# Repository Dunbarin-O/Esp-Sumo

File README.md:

# Esp-Sumo
## Design Story

Building a custom mini-sumo robot sounded straightforward until i tried try wiring one together. Early in the process, I realized that relying on a disconnected stack of off-the-shelf motor drivers, sensor breakout boards, and external voltage regulators created a fragile spiderweb of jumper wires that easily disconnected during testing also pretty ugly, very ugly. To build something that stayed together, I decided to design a single, custom printed circuit board (PCB) to integrate every subsystem onto one reliable platform.

My first major challenge was in designing the power architecture. I initially planned to use two high-efficiency switching buck converters in series one to drop the 7.4V battery down to 5V, and a second to drop it further to 3.3V. While it looked ideal in block diagrams, routing the PCB layout showed that the second converter added significant cost, component count, and board space for a negligible boost in efficiency. I pivoted to a hybrid design: a single switching converter for high-draw 5V motor and servo demands, paired with a lightweight linear regulator for sensitive 3.3V logic. This trade-off taught me balancing performance, cost, and simplicity

Seeking external feedback proved equally transformative. After completing my first schematic draft, I had another hardware designer review my work. That peer review exposed critical real-world edge cases I had completely overlooked. To prevent catastrophic shorts during rapid battery swaps, I incorporated a low-resistance P-channel MOSFET switch for instant reverse-polarity protection. I also completely re-evaluated my motor drivers. My initial plan used tiny DRV8220 drivers to keep the board compact, but testing showed their high internal resistance caused severe overheating, and their strict overcurrent protection completely shut off power during motor stalls. I upgraded to dual DRV8870 drivers featuring active "current chopping." Instead of shutting down when pushing against an obstacle, the new drivers automatically throttle current to deliver maximum safe pushing force without crashing the battery rail.

When the fabricated boards arrived, the ESP32-S3 microcontroller powered on and flashed code over USB smoothly on the first try. However, physical hardware quickly revealed real-world oversights that software DRC checks could not predict. I had selected incorrect physical footprints for my pin headers in KiCad, meaning the OLED display could not plug directly into the board and required manual jumper wire reworks. Furthermore, placing every component on a single side made the overall PCB footprint far too large for a compact mini-sumo chassis.

This project proved that a circuit can look entirely correct in a schematic editor while real-world physics, ergonomics, and physical dimensions tell a different story. Version 1 was not perfect, but it served as a functional masterclass in circuit protection, component selection, and practical board layout. For Version 2, I am transitioning to a double-sided component layout to cut the board size in half while correcting all header footprints for a clean, plug-and-play assembly.
---

### Read Further

For detailed technical implementation, schematics, component calculations, PCB layout files, and manufacturing outputs, explore the rest of the repository which is still a wip :

* **`PCB/`** – Native KiCad design files:
  * `Mini_sumo.kicad_sch` – Schematic capture files.
  * `Mini_sumo.kicad_pcb` – PCB trace routing and board layout.
* **`Hardware/`** – Assembly and manufacturing outputs:
  * `Mini_sumo.zip` – Production Gerber & drill files for board fabrication.
  * `combined_bom.csv` – Bill of Materials listing all active and passive components.
  * `positions.csv` – Pick-and-Place (CPL / Centroid) file for automated SMT assembly.
Project is in
 its early stages 

A low-cost, open-source motion control board for ESP32-based robots.
High-performance motor boards are usually expensive or made for just one job. This project is a low-cost, all-in-one board that lets you build precise small robots without needing extra shields or breakout boards.

Applications:

Mini Sumo Robots: Integrated motor control and gyro feedback for rapid opponent tracking and high-torque maneuvers.

Inverted Pendulum / Self-Balancing: Direct IMU integration for low-latency loop control and pitch stabilization.

Heading-Corrected Rovers: Closed-loop yaw monitoring for straight-line differential driving and precise turn angles.

### V1 Key Features

* **Dual High-Current Motor Drivers:** Two TI DRV8870 ICs providing independent PWM speed and direction control, supporting up to 3.6 A peak output per channel.
* **Onboard Motion Sensing:** MPU-6050 6-axis gyroscope and accelerometer connected via I2C for pitch, roll, and yaw feedback.
* **Integrated Diagnostic Display Header:** Dedicated 4-pin I2C header positioned for direct SSD1306 OLED screens (128x64 or 128x32).
* **User Input Controls:** 3 onboard tactical pushbuttons mapped to ESP32 GPIOs for mode selection, calibration, and menu navigation.
* **Built-in Servo Mount & Header:** Dedicated 3-pin PWM servo header (VCC, GND, Signal) with mounting holes integrated directly into the PCB outline (ideal for mini sumo flippers or sensor sweepers).
* **Optimized Power Architecture:** Designed for 2S (7.4V) LiPo input with onboard voltage regulation to safely power the ESP32, OLED, and logic components.
* **Expansion I/O:** Exposed GPIO headers for IR edge sensors, line detectors, or custom sensors.
* **100% Open-Source Hardware:** Full KiCad project files, schematics, PCB layouts, BOM, and manufacturing outputs (Gerbers/CPL) included.

| ESP32-S3 GPIO | Schematic net | Actually connected to             |
| ------------: | ------------- | --------------------------------- |
|     **GPIO0** | I00           | Boot button **SW3** + 10k pull-up |
|     **GPIO1** | D1            | **Right IR sensor** J5            |
|     **GPIO2** | D2            | **Left IR sensor** J6             |
|     **GPIO3** | D3            | **SW4 button**                    |
|     **GPIO4** | D4            | **Left edge sensor** J8           |
|     **GPIO5** | D5            | **Right edge sensor** J10         |
|     **GPIO6** | D6            | **SW5 button**                    |
|     **GPIO7** | D7            | **SW6 button**                    |
|     **GPIO8** | D8            | **Left motor driver IN2**         |
|     **GPIO9** | D9            | **Left motor driver IN1**         |
|    **GPIO10** | D10           | **J17 breakout pin 1**            |
|    **GPIO11** | D11           | **Gyro SCL**                      |
|    **GPIO12** | D12           | **Gyro SDA**                      |
|    **GPIO13** | D14           | **Right motor driver IN2**        |
|    **GPIO14** | D13           | **Right motor driver IN1**        |
|    **GPIO15** | D15           | **J15 / right motor?**            |
|    **GPIO16** | D16           | **J11 servo?**                    |
|    **GPIO17** | D17           | **J17 software uvlo**             |
|    **GPIO18** | D18           | **Servo signal**                  |
|    **GPIO19** | USB_D−        | **USB D−**                        |
|    **GPIO20** | USB_D+        | **USB D+**                        |
|    **GPIO21** | —             | **Unused**                        |

 ## Engineering Design Process & Iterations
## Power Design Choice: Dual Buck Converters vs. Buck + LDO

### First Attempt: Two-Stage Buck Regulation
My initial plan was to use two buck converters in series to drop the 7.4V (2S LiPo) battery voltage down to 5V, and then down to 3.3V for the system ICs to maximize energy efficiency.

**The Problem:** Each buck converter requires its own dedicated supporting passives (inductors, filter capacitors, and feedback resistors). Running two switching stages took up too much PCB footprint, added significant routing complexity, and increased the overall Bill of Materials (BOM) cost.

---

### Final Solution: Single Buck + 3.3V LDO Regulator
I simplified the power tree by keeping a single buck converter for the 5V rail and replacing the second buck stage with a straightforward 3.3V Low-Dropout (LDO) linear regulator.

## Peer Design Review: Power & Protection Enhancements

Following the V1 layout release, a community hardware review identified several critical power delivery and protection improvements to increase reliability:

### 1. Battery Input & System Protection
* **Circuit Protection:** The design was solid, but it lacked input safety. Adding an in-line fuse and a reverse-polarity protection circuit (e.g., a P-channel MOSFET or ideal diode) on the 2S LiPo rail is essential to prevent permanent board failure from accidental battery misplugs during quick pit stops.
* **Input Bulk Decoupling:** The 10 µF input capacitor ($C_{\text{IN}1}$) on the buck regulator followed basic bench-supply reference designs. However, long battery wire harnesses introduce parasitic inductance. Upgrading $C_{\text{IN}1}$ to a **47 µF ceramic + 10 µF ceramic paired with a 100 µF electrolytic** lowers High-Frequency ESR and prevents sudden motor current draw from sagging the shared battery rail and browning out the ESP32.

### 2. Switching Regulator Duty Cycle & Stability
* At 7.4 V nominal input, the 5 V buck converter operates near a **0.67 duty cycle** (higher as the LiPo drains). Because the regulator uses peak current mode with fixed internal compensation, switch-node signal integrity must be verified under full load with an oscilloscope to ensure stable loop performance across the entire discharge curve.

### 3. ESD & Port Safety
* Added dedicated **ESD protection IC (USBLC6-2SC6)** on the USB-C $V_{\text{BUS}}$ and $D+/D-$ lines to guard the ESP32 against static discharge during  flashing
* 

### Power Isolation: OR-ing Diode Selection

To prevent backfeeding power between the USB-C 5V supply and the onboard 5V buck converter when both are plugged in simultaneously, I implemented a simple diode OR-ing power path
combining the 2 into 5V Safe and feeding it into ldo.

* **Why Schottky over Silicon Diodes:** Standard silicon rectifiers cause a ~0.7V drop, which would reduce the 5.0V USB rail down to 4.3V—dangerously close to the ESP32's minimum operating threshold and brownout limit.
* **Low Forward Voltage ($V_F$):** Using Schottky diodes keeps the voltage drop under ~0.3V, maintaining a stable supply rail (~4.7V+) for logic components and sensors while safely preventing reverse current flow into your computer's USB port or the buck regulator since a lipo battery is used trying to charge over usb withour any charging circuits could be dangerous.
  
### Front-End Power Protection Circuit

* **P-Channel Reverse Polarity Protection (AO3401A):** Uses a low-$R_{DS(on)}$ P-FET (Q1) to block reverse voltage if the battery is plugged in backward, with a 10V Zener diode (D1) protecting $V_{GS}$ against voltage transients.
* **Overcurrent Safety (F1):** In-line fuse provides hard fault protection against high-current shorts.
* **Active Under-Voltage Monitoring (TPS3702):** Samples battery rail via resistor divider (R21/R22) and outputs a low-battery alert signal (D17) to the ESP32 to prevent over-discharging 2S LiPo cells.
* 
## Picking a driver IC : DRV8220 vs. DRV8870

When designing the motor stage, I needed driver chips capable of handling high startup currents and heavy mechanical loads without overheating or shutting down mid-operation.

### First Attempt: Dual DRV8220 (Compact, but Limited)

My initial plan was to use two compact DRV8220 drivers in the DRL package, but bench analysis revealed major bottlenecks:
* **Thermal Overheating:** High internal resistance ($R_{DS(on)} \approx 1\,\Omega$) and the lack of a thermal pad ($152\,^{\circ}\text{C/W}$ thermal resistance) caused severe heat buildup, limiting continuous current to $< 0.9\text{A}$.
* **Hard Shutdowns:** The $1.76\text{A}$ overcurrent protection (OCP) cuts power entirely during high loads or stalls, stopping the robot mid-operation instead of sustaining torque.
* **Difficult Hand-Soldering:** The tiny leadless DRL package has contacts tucked under the chip, making it extremely difficult to solder, inspect, or rework with a standard soldering iron without bridging.
* **No Built-in Current Sensing:** Lacks a dedicated `ISEN` pin, preventing the use of external sense resistors to measure or actively control motor current.
* **Startup Voltage Glitches & Efficiency Loss:** Logic inputs easily float during microcontroller boot, causing motor twitches. High internal resistance also wastes battery voltage as heat before it reaches the motors.

---

### Final Solution: Dual DRV8870 (High Power & Current Chopping)

I upgraded to two DRV8870 drivers featuring an exposed PowerPAD package and external sense resistors:
* **Hand-Soldering Friendly:** The larger HSOP-8 package with exposed leads **very** important for reliable hand soldering(ended up having it assembled by jcl).
* **Superior Thermals:** Lower internal resistance ($450\,\text{m}\Omega$) paired with a copper thermal pad handles up to $3.6\text{A}$ peak current safely.
* 

* **Smart Current Chopping ($I_{\text{TRIP}}$):** Instead of shutting down completely during a stall, the driver uses parallel sense resistors ($R17 - R20$) totaling $0.2\,\Omega$ to limit current automatically:
  $$I_{\text{TRIP}} = \frac{V_{\text{REF}}}{10 \times R_{\text{ISEN}}} = \frac{3.3\text{V}}{10 \times 0.2\,\Omega} = 1.65\text{A}$$
  When pushing heavy loads, the chip acts like an automatic safety valve "chopping" current to maintain pushing force without tripping power failures or browning out the battery rail.
* **Brush Noise Suppression:** Added $0.1\,\mu\text{F}$ ceramic capacitors ($C2, C5$) directly across the motor terminals to absorb high-frequency electrical noise before it can interfere with the I2C gyroscope or IR floor sensors.

---
## ESP32-S3 Core
i chose the s3 because of its native usb to uart and it simplicity to set up and get working keeping parts cost low

This section covers the core ESP32-S3 microcontroller, its power filtering, boot/reset logic, user UI, and external expansion headers.

### Core Microcontroller (ESP32-S3-WROOM-1)
* **Brain of the Robot:** Handles sensor polling, motor control loops, and peripheral interfaces.
* **Power Decoupling ($C14, C15$):** Placed $0.1\,\mu\text{F}$ and $22\,\mu\text{F}$ capacitors close to the $+3.3\text{V}$ power pin (`Pin 2`) to filter out high-frequency noise and prevent voltage dips when the chip spikes in power draw during wireless tasks or bootup.

---

### Boot Logic & System Buttons
* **Reset Circuit (`SW2`, `EN`):** Pressing `SW2` pulls the `EN` pin to ground to manually restart the microcontroller. 
  * **Debouncing & RC Delay ($R9, C9, C13, R13$):** An RC circuit ($10\,\text{k}\Omega$ pull-up + $1\,\mu\text{F}$ cap) keeps `EN` stable at $+3.3\text{V}$ and prevents electrical noise from causing random micro-resets.
* **Boot Button (`SW3`, `IO0`):** Pressing `SW3` grounds `IO0` on startup to force the ESP32 into USB flashing/bootloader mode. A $10\,\text{k}\Omega$ pull-up resistor ($R14$) ensures `IO0` stays pulled HIGH during normal operation so the chip boots standard code.

---

### User UI & Peripherals
* **User Pushbuttons (`SW4`, `SW5`, `SW6`):** Standard tactile buttons tied to `D3`, `D6`, and `D7`. When pressed, they ground the input line, giving the user programmable controls (e.g., selecting robot fight modes or starting a match).
* **Status LED (`D6`, $R15$):** A debug LED connected to $+3.3\text{V}$ via a $1\,\text{k}\Omega$ current-limiting resistor ($R15$) for visual feedback.

---

### Breakout & Expansion Headers
* **Power Breakouts (`J7`, `J9`):** 4-pin headers giving easy access to GND and $+3.3\text{V}$ rails for external modules, logic analyzers, or multimeters during bench testing.
* **OLED / Sensor Connector (`J17`):** 4-pin connector routing $+3.3\text{V}$, GND, `D10`, and `D17` for plugging in external displays or additional sensor modules.
* **Servo Connector (`J11`):** Dedicated 3-pin header routing $+5\text{V}$, GND, and signal line `D18` to drive a servo motor directly.
## Final Schematic

## Board in Hand: Lessons & Physical Hardware Issues

Testing the physical V1 board revealed several layout footprint mismatches and routing constraints that required manual rework:

* **Header Pin Size Mismatches:** The physical pin header footprints for GND, 3.3V, breakout points, and the OLED screen connector were sized incorrectly compared to the actual component pitch/pin sizes.
* **OLED Screen Rework:** Because of the pin size mismatch at header `J17`, the display could not be mounted directly to the PCB. As a temporary workaround, jumper wires had to be manually soldered to interface the screen with the board.
* **Large Board Footprint:** Things **HUGE!**
* **Next Version Improvements:** V2 will utilize double-sided SMT component placement to shrink the board footprint significantly, alongside corrected pin header footprints to eliminate wire jumpers.
##Testing & Peripheral Hardware Validation

 For the buttons 
 i use micropython and thonny the arduiono ide would work just fine
 Thonny.

### Interactive Reflex Game
An interactive MicroPython script that measures reaction times in milliseconds using `time.ticks_ms()` to stress-test button responsiveness under dynamic polling loop conditions.

```python
#MADE FOR MICROPYTHON 
Python
import time
import random
from machine import Pin

# Initialize switches with internal pull-ups (Active LOW)
switches = {
    "SW4 (IO3)": Pin(3, Pin.IN, Pin.PULL_UP),
    "SW5 (IO6)": Pin(6, Pin.IN, Pin.PULL_UP),
    "SW6 (IO7)": Pin(7, Pin.IN, Pin.PULL_UP),
}

print("=" * 40)
print("   MINI-SUMO BUTTON REFLEX CHALLENGE")
print("=" * 40)
print("Instructions: Press the requested button as fast as possible when prompted!\n")

time.sleep(2)

score = 0
total_rounds = 5

for r in range(1, total_rounds + 1):
    print(f"\n--- ROUND {r} of {total_rounds} ---")
    print("Get ready...")
    
    # Wait a random delay (1.5 to 4 seconds) to prevent guessing
    time.sleep(random.uniform(1.5, 4.0))
    
    # Select a target button randomly
    target_name, target_pin = random.choice(list(switches.items()))
    
    print("\n" + "#" * 30)
    print(f"   ---> PRESS {target_name}! <---")
    print("#" * 30)
    
    start_time = time.ticks_ms()
    pressed = False
    
    while not pressed:
        # Check all switches
        for name, pin in switches.items():
            if pin.value() == 0:  # Button pressed (LOW)
                reaction_time = time.ticks_diff(time.ticks_ms(), start_time)
                
                if name == target_name:
                    print(f"SUCCESS! Reaction Time: {reaction_time} ms")
                    score += 1
                else:
                    print(f"WRONG BUTTON! You pressed {name} instead of {target_name}. (+0 pts)")
                
                pressed = True
                
                # Debounce / wait until button is released before moving on
                while pin.value() == 0:
                    time.sleep_ms(10)
                break
                
        time.sleep_ms(5)  # Polling delay

    time.sleep(1)

print("\n" + "=" * 40)
print(f"GAME OVER! Final Score: {score} / {total_rounds}")
if score == total_rounds:
    print("Rating: SUMO GRAND CHAMPION (Lightning fast!)")
elif score >= 3:
    print("Rating: SOLID REFLEXES")
else:
    print("Rating: NEEDS PRACTICE")
print("=" * 40)
```
## Servo Test Script

This script verifies manual servo position control using pushbuttons connected to **GPIO 3** (SW4), **GPIO 6** (SW5), and **GPIO 7** (SW6). It controls the servo signal line on **GPIO 18**. 

* **Note:** i Had to bypass a tight spot on the board by jumping signals directly with jumper wires during testing.

```python
import time
from machine import PWM, Pin

# Servo setup on GPIO 18 (D18)
servo_pin = Pin(18, Pin.OUT)
servo_pwm = PWM(servo_pin)
servo_pwm.freq(50)

# Switches configured with internal pull-ups (Active LOW)
sw4 = Pin(3, Pin.IN, Pin.PULL_UP)  # SW4 -> 0 deg
sw5 = Pin(6, Pin.IN, Pin.PULL_UP)  # SW5 -> 90 deg
sw6 = Pin(7, Pin.IN, Pin.PULL_UP)  # SW6 -> 180 deg

def set_angle(angle):
    angle = max(0, min(180, angle))
    # Map 0-180 deg to 16-bit PWM duty (1638 = 0.5ms, 8192 = 2.5ms at 50Hz)
    duty = int(1638 + (angle / 180.0) * (8192 - 1638))
    servo_pwm.duty_u16(duty)

# Move to center position on boot
set_angle(90)

print("Servo Button Test Active on GPIO 18")
print("Press SW4 (GPIO 3) -> 0° | SW5 (GPIO 6) -> 90° | SW6 (GPIO 7) -> 180°")

while True:
    if sw4.value() == 0:
        set_angle(0)
        print("SW4 Pressed -> Servo set to 0°")
        while sw4.value() == 0:  # Debounce hold
            time.sleep_ms(10)

    elif sw5.value() == 0:
        set_angle(90)
        print("SW5 Pressed -> Servo set to 90°")
        while sw5.value() == 0:
            time.sleep_ms(10)

    elif sw6.value() == 0:
        set_angle(180)
        print("SW6 Pressed -> Servo set to 180°")
        while sw6.value() == 0:
            time.sleep_ms(10)

    time.sleep_ms(20)

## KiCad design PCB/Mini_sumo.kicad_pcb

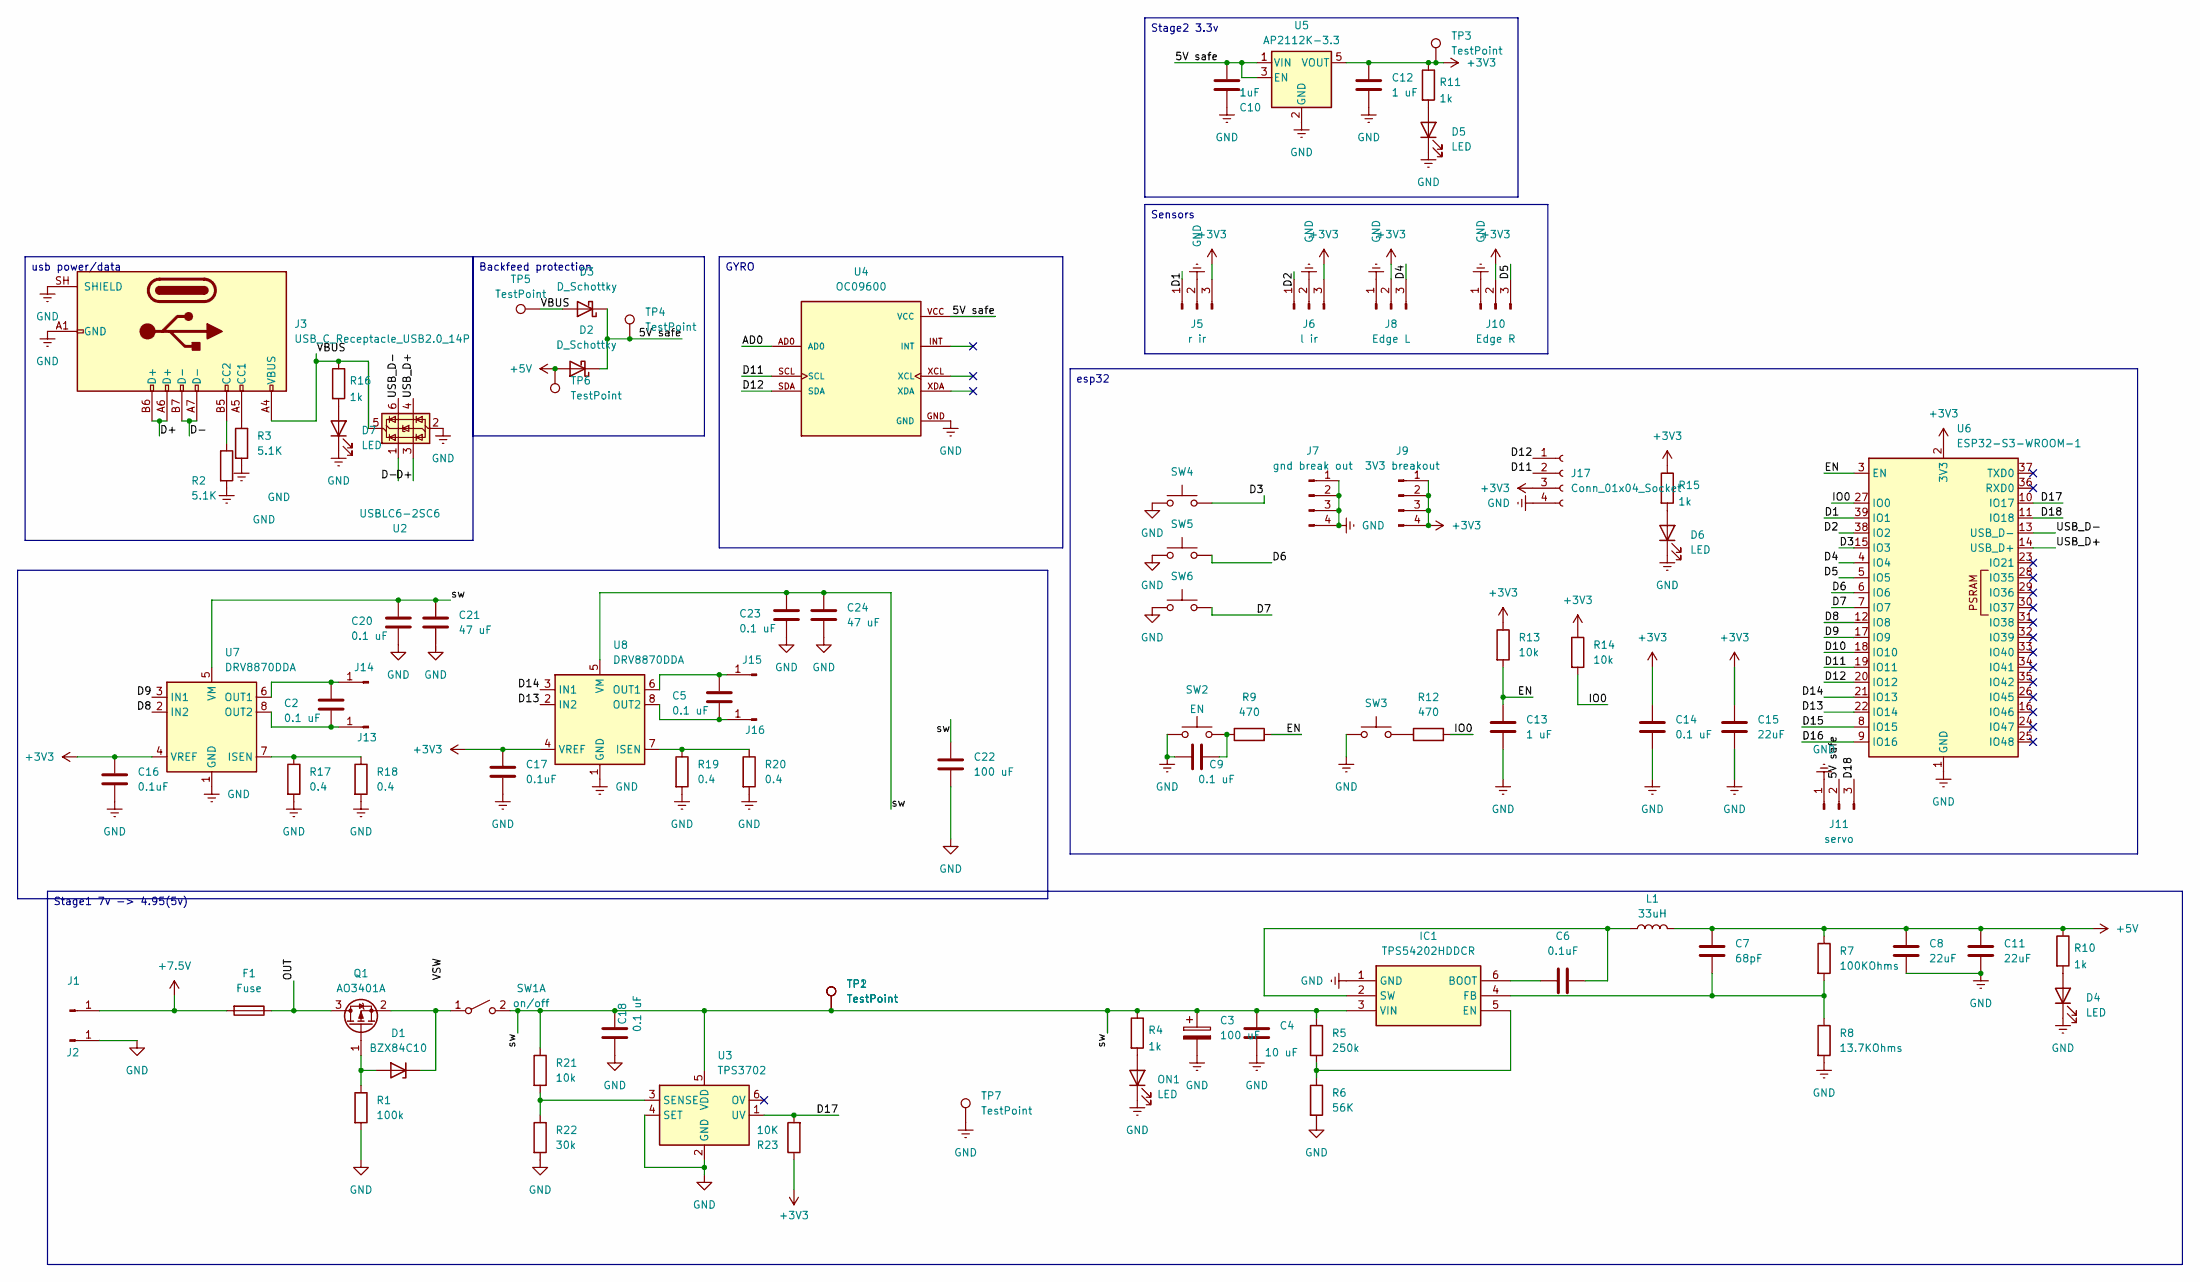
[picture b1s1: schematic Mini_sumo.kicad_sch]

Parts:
C2, C5, C9, C14, C18, C20, C23: 0.1 uF; C_1206_3216Metric_Pad1.33x1.80mm_HandSolder
C3, C22: 100 uF; C_1210_3225Metric_Pad1.33x2.70mm_HandSolder
C4: 10 uF; C_1206_3216Metric
C6, C16, C17: 0.1uF; C_1206_3216Metric_Pad1.33x1.80mm_HandSolder
C7: 68pF; C_1206_3216Metric_Pad1.33x1.80mm_HandSolder
C8, C11, C15: 22uF; C_1210_3225Metric_Pad1.33x2.70mm_HandSolder
C10: 1uF; C_1206_3216Metric_Pad1.33x1.80mm_HandSolder
C12, C13: 1 uF; C_1206_3216Metric_Pad1.33x1.80mm_HandSolder
C21, C24: 47 uF; C_1210_3225Metric_Pad1.33x2.70mm_HandSolder
D1: BZX84C10; SOT-23-3
D2, D3: D_Schottky; D_SMA-SMB_Universal_Handsoldering
D4, D5, D6, D7: LED; LED_0805_2012Metric_Pad1.15x1.40mm_HandSolder
F1: Fuse; Fuse_1812_4532Metric_Pad1.30x3.40mm_HandSolder
IC1: TPS54202HDDCR; IC1; Mouser Part Number 595-TPS54202HDDCR
J1, J2, J13, J14, J15, J16: Conn_01x01_Pin; SolderWirePad_1x01_SMD_5x10mm
J3: USB_C_Receptacle_USB2.0_14P; USB_C_Receptacle_HCTL_HC-TYPE-C-16P-01A
J5: r ir; JST_PH_B3B-PH-K_1x03_P2.00mm_Vertical
J6: l ir; JST_PH_B3B-PH-K_1x03_P2.00mm_Vertical
J7: gnd break out; PinHeader_1x03_P1.27mm_Vertical
J8: Edge L; JST_PH_B3B-PH-K_1x03_P2.00mm_Vertical
J9: 3V3 breakout; PinHeader_1x03_P1.27mm_Vertical
J10: Edge R; JST_PH_B3B-PH-K_1x03_P2.00mm_Vertical
J11: servo; PinHeader_1x03_P1.27mm_Vertical
J17: Conn_01x04_Socket; PinHeader_1x04_P1.27mm_Vertical
L1: 33uH; L_Bourns_SRP7028A_7.3x6.6mm
ON1: LED; LED_0805_2012Metric_Pad1.15x1.40mm_HandSolder
Q1: AO3401A; SOT-23
R1: 100k; R_1210_3225Metric_Pad1.30x2.65mm_HandSolder
R2, R3: 5.1K; R_1210_3225Metric_Pad1.30x2.65mm_HandSolder
R4, R10, R11, R15, R16: 1k; R_1210_3225Metric_Pad1.30x2.65mm_HandSolder
R5: 250k; R_1210_3225Metric_Pad1.30x2.65mm_HandSolder
R6: 56K; R_1210_3225Metric_Pad1.30x2.65mm_HandSolder
R7: 100KOhms; R_1210_3225Metric_Pad1.30x2.65mm_HandSolder
R8: 13.7KOhms; R_1210_3225Metric_Pad1.30x2.65mm_HandSolder
R9, R12: 470; R_1210_3225Metric_Pad1.30x2.65mm_HandSolder
R13, R14, R21: 10k; R_1210_3225Metric_Pad1.30x2.65mm_HandSolder
R17, R18, R19, R20: 0.4; R_1206_3216Metric
R22: 30k; R_1210_3225Metric_Pad1.30x2.65mm_HandSolder
R23: 10K; R_1210_3225Metric_Pad1.30x2.65mm_HandSolder
SW1: on/off; SW_Slide_SPDT_Angled_CK_OS102011MA1Q
SW2: EN; SW_Push_SPST_NO_Alps_SKRK
SW3, SW4, SW5, SW6: SW_Push; SW_Push_SPST_NO_Alps_SKRK
TP1, TP2, TP3, TP4, TP5, TP6, TP7: TestPoint; TestPoint_Pad_1.5x1.5mm
U2: USBLC6-2SC6; SOT-23-6
U3: TPS3702; SOT-23-6
U4: OC09600; MODULE_OC09600; PARTREV NA
U5: AP2112K-3.3; SOT-23-5
U6: ESP32-S3-WROOM-1
U7, U8: DRV8870DDA; Texas_HTSOP-8-1EP_3.9x4.9mm_P1.27mm_EP2.95x4.9mm_Mask2.4x3.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

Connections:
+3V3: C12.1, C14.1, C15.1, C16.2, C17.2, J5.3, J6.3, J8.2, J9.1, J9.2, J9.3, J9.4, J10.2, J17.3, R11.1, R13.1, R14.1, R15.1, R23.1, TP3.1 (1_1), U5.5 (VOUT), U6.2 (3V3), U7.4 (VREF), U8.4 (VREF)
+5V: C7.1, C8.1, C11.1, D2.2 (A), L1.2, R7.1, R10.1, TP6.1 (1_1)
+7.5V: F1.2, J1.1 (Pin_1_1)
/5V safe: C10.1, D2.1 (K), D3.1 (K), J11.2, TP4.1 (1_1), U4.VCC, U5.1 (VIN), U5.3 (EN); also elsewhere on the board
/AD0: U4.AD0
/D1: J5.1, U6.39 (IO1)
/D2: J6.1, U6.38 (IO2)
/D3: SW4.2, U6.15 (IO3)
/D4: J8.3, U6.4 (IO4)
/D5: J10.3, U6.5 (IO5)
/D6: SW5.2, U6.6 (IO6)
/D7: SW6.2, U6.7 (IO7)
/D8: U6.12 (IO8), U7.2 (IN2)
/D9: U6.17 (IO9), U7.3 (IN1)
/D10: U6.18 (IO10)
/D11: J17.2, U4.SCL, U6.19 (IO11)
/D12: J17.1, U4.SDA, U6.20 (IO12)
/D13: U6.22 (IO14), U8.2 (IN2)
/D14: U6.21 (IO13), U8.3 (IN1)
/D15: U6.8 (IO15)
/D16: U6.9 (IO16)
/D17: R23.2, U3.1 (UV), U6.10 (IO17)
/D18: J11.3, U6.11 (IO18); also elsewhere on the board
/D+: J3.A6 (D+), J3.B6 (D+), U2.3 (I/O2)
/D-: J3.A7 (D-), J3.B7 (D-), U2.1 (I/O1)
/EN: C13.1, R9.2, R13.2, U6.3 (EN)
/IO0: R12.2, R14.2, U6.27 (IO0)
/OUT: F1.1, Q1.3 (D)
/USB_D+: U2.4 (I/O2), U6.14 (USB_D+)
/USB_D-: U2.6 (I/O1), U6.13 (USB_D-)
/VBUS: D3.2 (A), J3.A4 (VBUS), J3.A9 (VBUS), J3.B4 (VBUS), J3.B9 (VBUS), R16.1, TP5.1 (1_1), U2.5 (VBUS)
/sw: C3.1, C4.1, C18.2, C20.1, C21.1, C22.1, C23.1, C24.1, IC1.3 (VIN), R4.1, R5.2, R21.1, SW1.2 (B), TP1.1 (1_1), TP2.1, U3.5 (VDD), U7.5 (VM), U8.5 (VM)
GND: C3.2, C4.2, C8.2, C9.1, C10.2, C11.2, C12.2, C13.2, C14.2, C15.2, C16.1, C17.1, C18.1, C20.2, C21.2, C22.2, C23.2, C24.2, D4.1 (K), D5.1 (K), D6.1 (K), D7.1 (K), IC1.1 (GND), J2.1 (Pin_1_1), J3.A1 (GND), J3.A12 (GND), J3.B1 (GND), J3.B12 (GND), J3.SH (SHIELD), J5.2, J6.2, J7.1, J7.2, J7.3, J7.4, J8.1, J10.1, J11.1, J17.4, ON1.1 (K), R1.2, R2.2, R3.2, R6.2, R8.2, R17.2, R18.2, R19.2, R20.2, R22.2, SW2.1, SW3.1, SW4.1, SW5.1, SW6.1, TP7.1, U2.2 (GND), U3.2 (GND), U3.4 (SET), U4.GND, U5.2 (GND), U6.1 (GND), U6.40 (GND), U6.41 (GND), U7.1 (GND), U7.9 (GND), U8.1 (GND), U8.9 (GND); also elsewhere on the board
unnamed: C9.2, R9.1, SW2.2
unnamed: D1.2 (A), Q1.1 (G), R1.1
unnamed: D1.1 (K), Q1.2 (S), SW1.1 (A)
unnamed: D4.2 (A), R10.2
unnamed: D5.2 (A), R11.2
unnamed: D6.2 (A), R15.2
unnamed: D7.2 (A), R16.2
unnamed: C6.1, IC1.6 (BOOT)
unnamed: IC1.5 (EN), R5.1, R6.1
unnamed: C7.2, IC1.4 (FB), R7.2, R8.1
unnamed: C6.2, IC1.2 (SW), L1.1
unnamed: J3.A5 (CC1), R3.1
unnamed: J3.B5 (CC2), R2.1
unnamed: C2.2, J13.1 (Pin_1_1), U7.8 (OUT2)
unnamed: C2.1, J14.1 (Pin_1_1), U7.6 (OUT1)
unnamed: C5.1, J15.1 (Pin_1_1), U8.6 (OUT1)
unnamed: C5.2, J16.1 (Pin_1_1), U8.8 (OUT2)
unnamed: ON1.2 (A), R4.2
unnamed: R12.1, SW3.2
unnamed: R21.2, R22.1, U3.3 (SENSE)
unnamed: R17.1, R18.1, U7.7 (ISEN)
unnamed: R19.1, R20.1, U8.7 (ISEN)

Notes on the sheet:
usb power/data
Stage1 7v -> 4.95(5v)
Stage2 3.3v
Sensors
GYRO
esp32
Backfeed protection

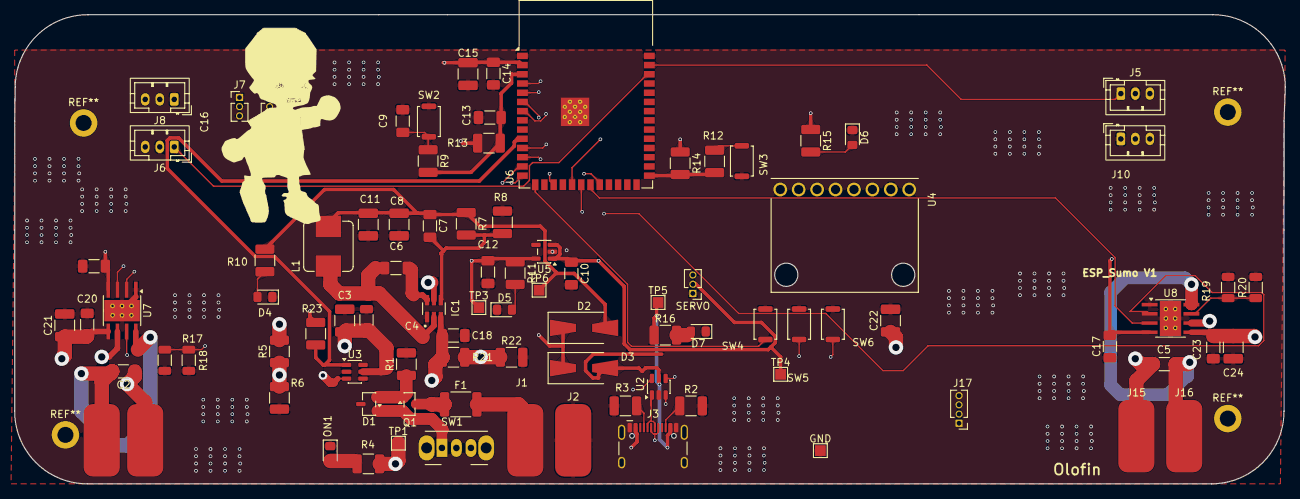
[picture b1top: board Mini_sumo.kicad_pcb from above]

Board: 4 copper layers, 175.2 x 64.7 mm, 91 parts (0 on the bottom side), 51 nets.

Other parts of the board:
GND: TestPoint; TestPoint_Pad_1.5x1.5mm
SERVO: servo; PinHeader_1x03_P1.27mm_Vertical

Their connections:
/5V safe: SERVO.2; also elsewhere on the board
/D18: SERVO.3; also elsewhere on the board
GND: GND.1 (1_1), SERVO.1; also elsewhere on the board

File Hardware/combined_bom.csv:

Comment,Designator,Footprint,Quantity,JLCPCB Part #
1uF,"C10, C12, C13",1206,3,C1848
22uF,"C8, C11, C15",1210,3,C19659
0.1 uF,"C2, C5, C6, C9, C14, C16, C17, C18, C20, C23",1206,10,C24497
47 uF,"C21, C24",1210,2,C76680
100 uF,"C3, C22",1210,2,C84455
10 uF,C4,1206,1,C13585
68pF,C7,1206,1,C107178
BZX84C10,D1,SOT-23-3,1,C19077470
D_Schottky,"D2, D3",D_SMA-SMB_Universal_Handsoldering,2,C2480
LED,"D4, D5, D6, D7, ON1",0805,5,C84256
Fuse,F1,1812,1,C3102
TPS54202HDDCR,IC1,IC1,1,C527684
USB_C_Receptacle_USB2.0_14P,J3,USB_C_Receptacle_HCTL_HC-TYPE-C-16P-01A,1,C165948
33uH,L1,L_Bourns_SRP7028A_7.3x6.6mm,1,C329385
AO3401A,Q1,SOT-23,1,C15127
100k,"R1, R7",1210,2,C620660
1k,"R4, R10, R11, R15, R16",1210,5,C270888
470,"R9, R12",1210,2,C137072
10k,"R13, R14, R21, R23",1210,4,C422430
0.4,"R17, R18, R19, R20",1206,4,C247521
5.1K,"R2, R3",1210,2,C2933867
30k,R22,1210,1,C728373
250k,R5,1210,1,C374782
56K,R6,1210,1,C147160
13.7KOhms,R8,1210,1,C54124
on/off,SW1,SW_Slide_SPDT_Angled_CK_OS102011MA1Q,1,C221530
EN,"SW2, SW3, SW4, SW5, SW6",SW_Push_SPST_NO_Alps_SKRK,5,C202388
USBLC6-2SC6,U2,SOT-23-6,1,C2827654
TPS3702,U3,SOT-23-6,1,C2068031
AP2112K-3.3,U5,SOT-23-5,1,C23380830
ESP32-S3-WROOM-1,U6,ESP32-S3-WROOM-1,1,C2913202
DRV8870DDA,"U7, U8",Texas_HTSOP-8-1EP_3.9x4.9mm_P1.27mm_EP2.95x4.9mm_Mask2.4x3.1mm_ThermalVias,2,C86590
TestPoint,"GND, TP1, TP3, TP4, TP5, TP6",TestPoint_Pad_1.5x1.5mm,6,
Conn_01x01_Pin,"J1, J2, J13, J14, J15, J16",SolderWirePad_1x01_SMD_5x10mm,6,
Edge R,J10,JST_PH_B3B-PH-K_1x03_P2.00mm_Vertical,1,
Conn_01x04_Socket,J17,PinHeader_1x04_P1.27mm_Vertical,1,
r ir,J5,JST_PH_B3B-PH-K_1x03_P2.00mm_Vertical,1,
l ir,J6,JST_PH_B3B-PH-K_1x03_P2.00mm_Vertical,1,
gnd break out,J7,PinHeader_1x03_P1.27mm_Vertical,1,
Edge L,J8,JST_PH_B3B-PH-K_1x03_P2.00mm_Vertical,1,
3V3 breakout,J9,PinHeader_1x03_P1.27mm_Vertical,1,
servo,SERVO,PinHeader_1x03_P1.27mm_Vertical,1,
OC09600,U4,MODULE_OC09600,1,
